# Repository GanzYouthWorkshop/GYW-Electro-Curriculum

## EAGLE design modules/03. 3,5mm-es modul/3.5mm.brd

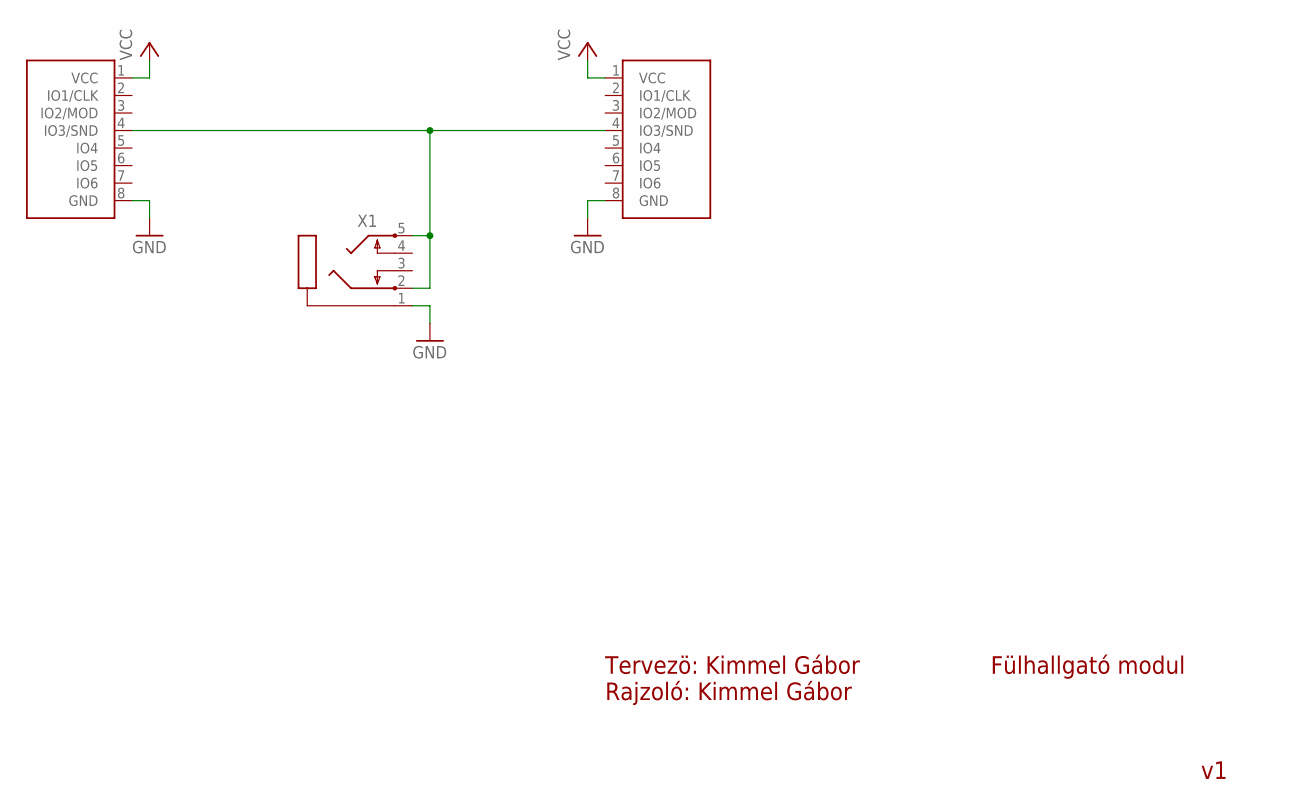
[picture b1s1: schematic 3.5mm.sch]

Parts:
U$1: GANZ-CONNECTOR; FE08W
U$2: GANZ-CONNECTOR-OUT; MA08-1W
X1: PG203J

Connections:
GND: U$1.8 (GND), U$2.8 (GND), X1.1
unnamed: U$1.4 (IO3/SND), U$2.4 (IO3/SND), X1.2, X1.5
VCC: U$1.1 (VCC), U$2.1 (VCC)

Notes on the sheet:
Fülhallgató modul
Tervezö: Kimmel Gábor Rajzoló: Kimmel Gábor

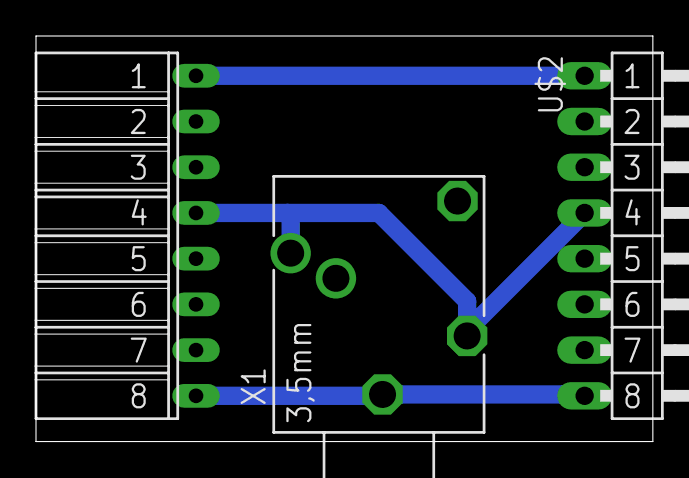
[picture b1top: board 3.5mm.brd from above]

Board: 2 copper layers, 34.3 x 22.5 mm, 3 parts (0 on the bottom side), 3 nets.

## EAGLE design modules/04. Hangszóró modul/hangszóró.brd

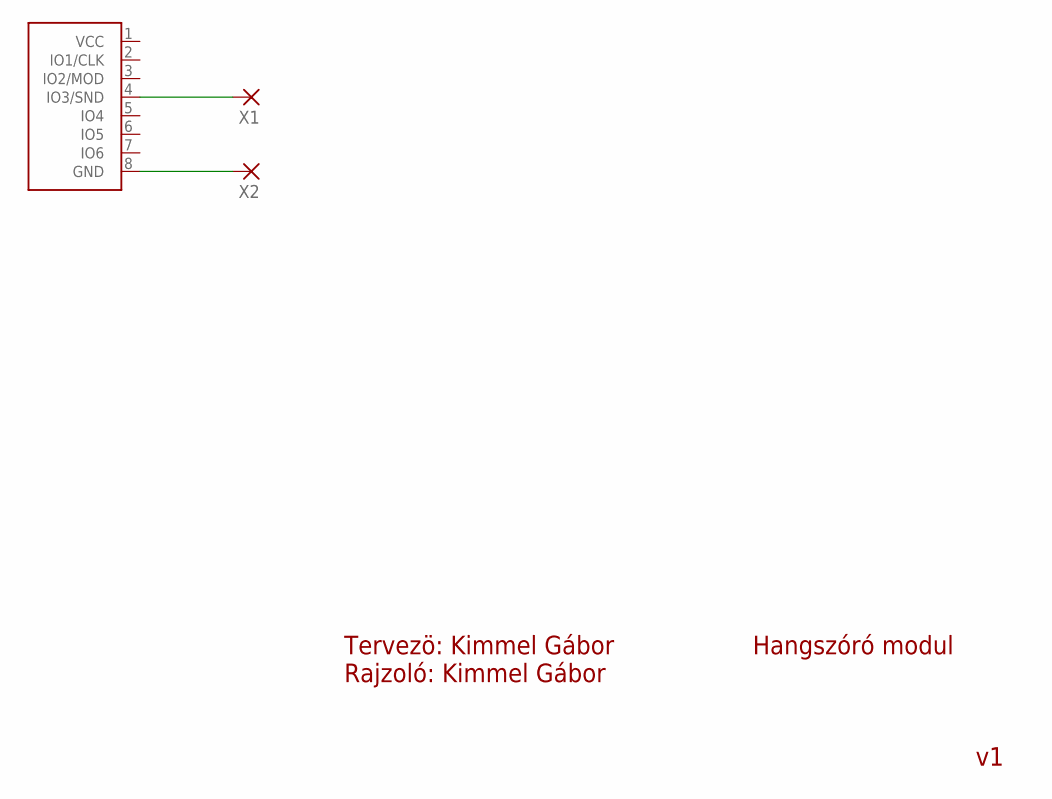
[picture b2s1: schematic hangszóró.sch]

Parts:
U$1: GANZ-CONNECTOR; FE08W
X1, X2: 2,15/1,0

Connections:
unnamed: U$1.4 (IO3/SND), X1.1
unnamed: U$1.8 (GND), X2.1

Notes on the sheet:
Hangszóró modul
Tervezö: Kimmel Gábor Rajzoló: Kimmel Gábor

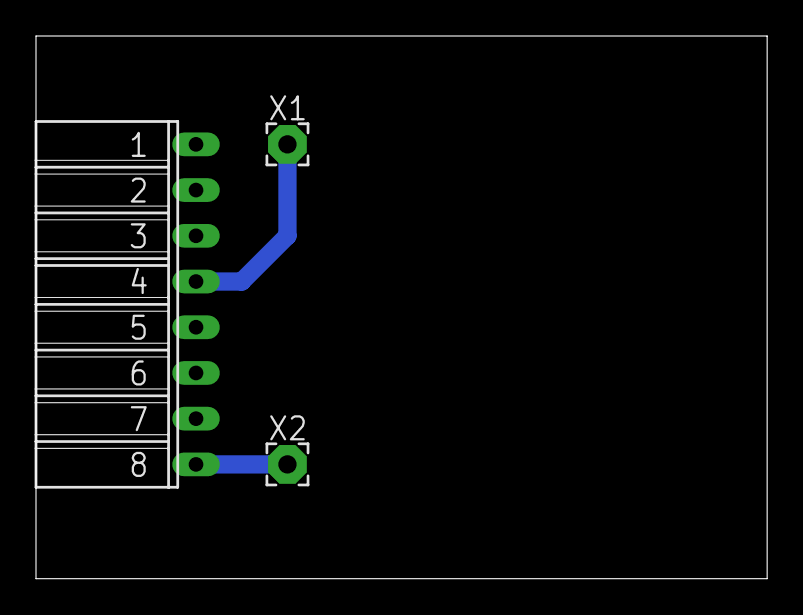
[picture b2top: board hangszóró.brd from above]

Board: 2 copper layers, 40.6 x 30.1 mm, 3 parts (0 on the bottom side), 2 nets.

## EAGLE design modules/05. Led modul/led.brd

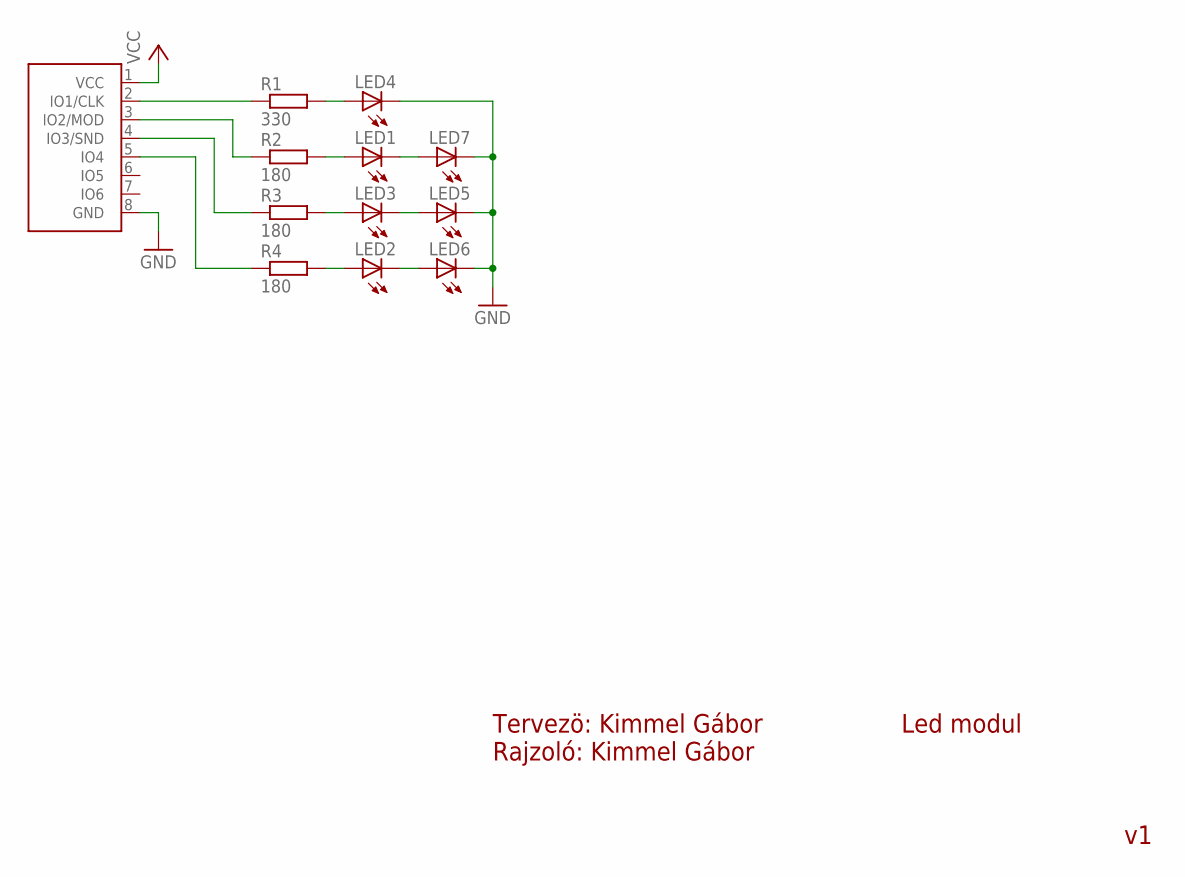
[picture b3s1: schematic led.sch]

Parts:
LED1, LED2, LED3, LED4, LED5, LED6, LED7: LED5MM
R1: 330; 0207/10
R2, R3, R4: 180; 0207/10
U$1: GANZ-CONNECTOR; FE08W

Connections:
GND: LED4.K (C), LED5.K (C), LED6.K (C), LED7.K (C), U$1.8 (GND)
unnamed: R1.1, U$1.2 (IO1/CLK)
unnamed: LED4.A, R1.2
unnamed: LED1.A, R2.2
unnamed: LED3.A, R3.2
unnamed: LED2.A, R4.2
unnamed: LED2.K (C), LED6.A
unnamed: LED3.K (C), LED5.A
unnamed: LED1.K (C), LED7.A
unnamed: R2.1, U$1.3 (IO2/MOD)
unnamed: R3.1, U$1.4 (IO3/SND)
unnamed: R4.1, U$1.5 (IO4)
VCC: U$1.1 (VCC)

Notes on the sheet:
Led modul
Tervezö: Kimmel Gábor Rajzoló: Kimmel Gábor

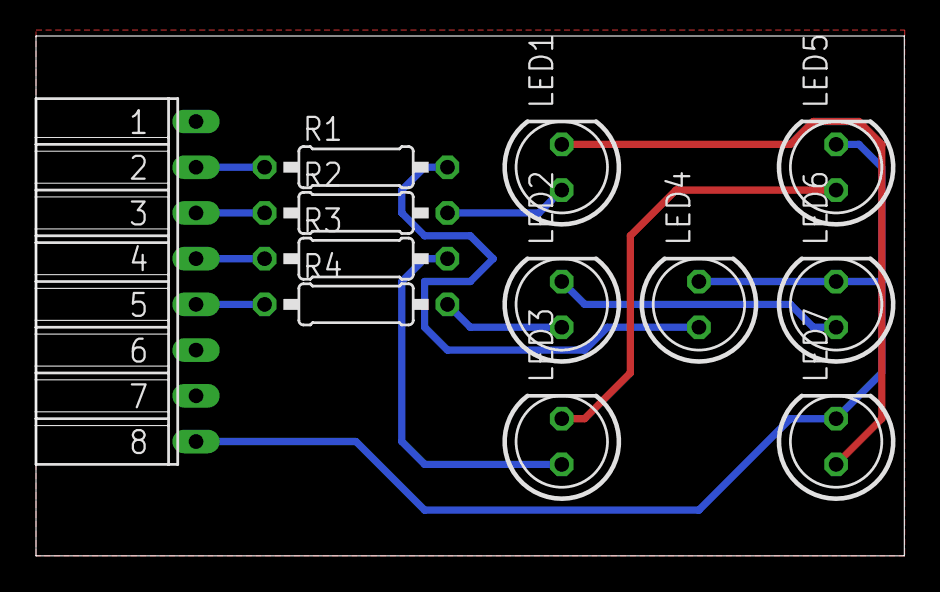
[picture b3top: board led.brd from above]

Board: 2 copper layers, 48.2 x 28.9 mm, 12 parts (0 on the bottom side), 12 nets.

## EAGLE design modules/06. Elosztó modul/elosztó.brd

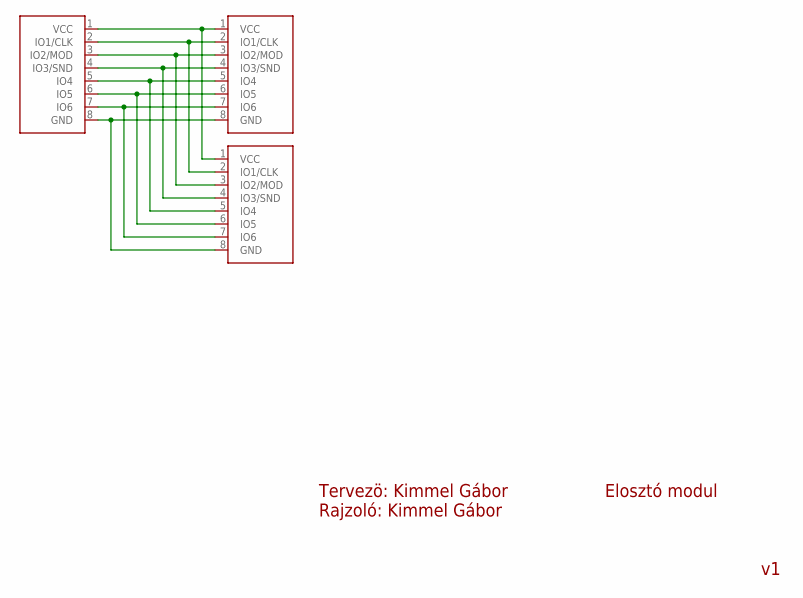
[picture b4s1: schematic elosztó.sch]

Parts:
U$1: GANZ-CONNECTOR; FE08W
U$2, U$3: GANZ-CONNECTOR-OUT; MA08-1W

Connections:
unnamed: U$1.1 (VCC), U$2.1 (VCC), U$3.1 (VCC)
unnamed: U$1.2 (IO1/CLK), U$2.2 (IO1/CLK), U$3.2 (IO1/CLK)
unnamed: U$1.3 (IO2/MOD), U$2.3 (IO2/MOD), U$3.3 (IO2/MOD)
unnamed: U$1.4 (IO3/SND), U$2.4 (IO3/SND), U$3.4 (IO3/SND)
unnamed: U$1.5 (IO4), U$2.5 (IO4), U$3.5 (IO4)
unnamed: U$1.6 (IO5), U$2.6 (IO5), U$3.6 (IO5)
unnamed: U$1.7 (IO6), U$2.7 (IO6), U$3.7 (IO6)
unnamed: U$1.8 (GND), U$2.8 (GND), U$3.8 (GND)

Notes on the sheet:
Elosztó modul
Tervezö: Kimmel Gábor Rajzoló: Kimmel Gábor

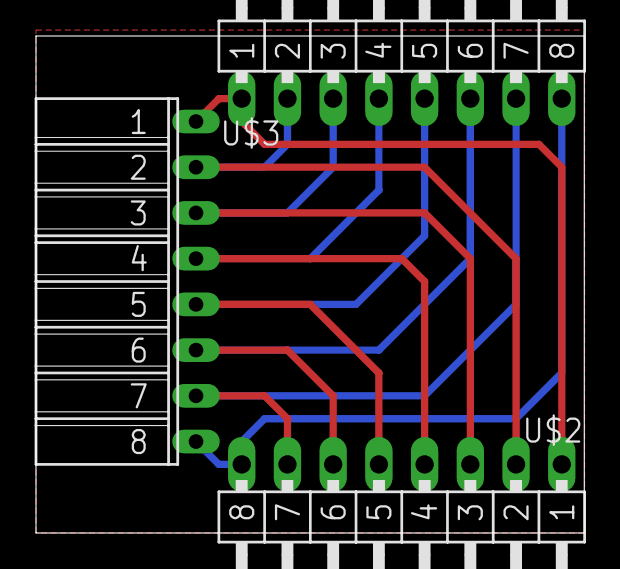
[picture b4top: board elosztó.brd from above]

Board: 2 copper layers, 30.5 x 27.6 mm, 3 parts (0 on the bottom side), 8 nets.

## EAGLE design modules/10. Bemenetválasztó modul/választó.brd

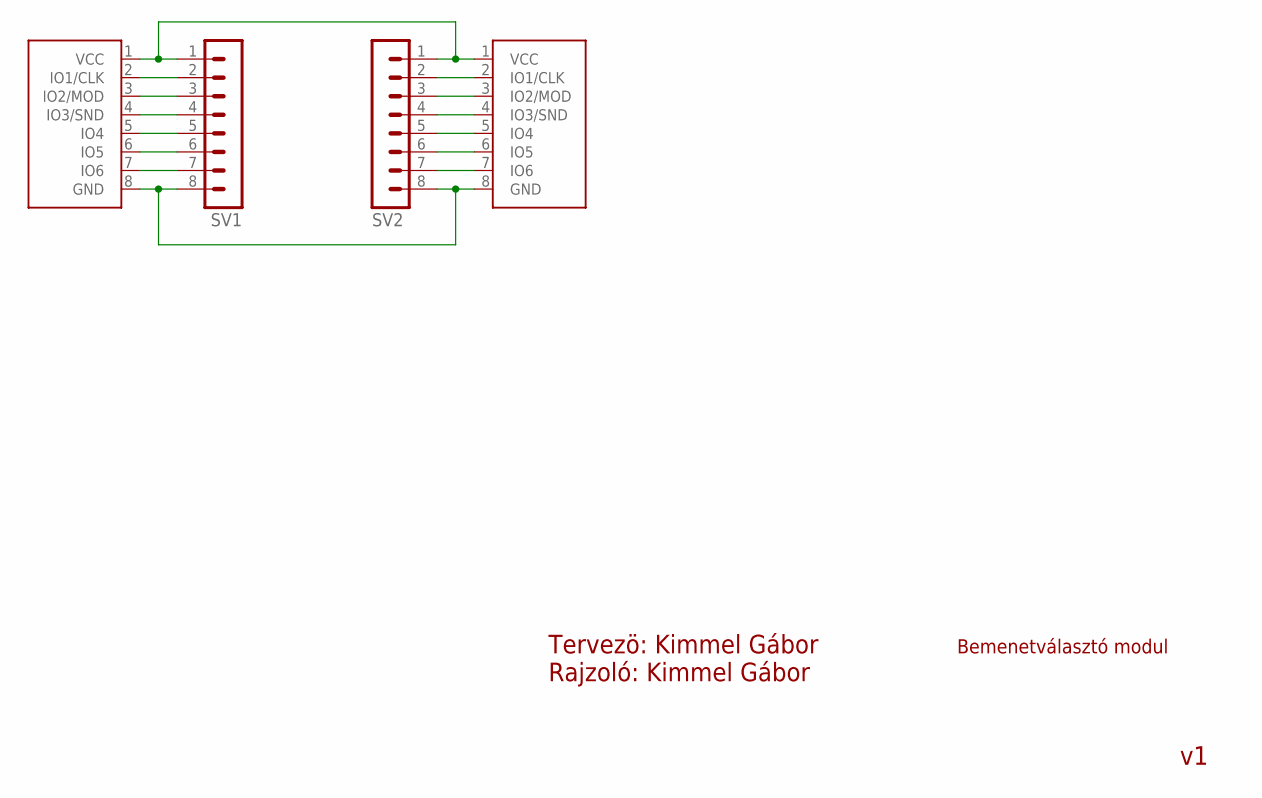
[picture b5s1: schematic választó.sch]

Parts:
SV1, SV2: MA08-1
U$1: GANZ-CONNECTOR; FE08W
U$2: GANZ-CONNECTOR-OUT; MA08-1W

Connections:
unnamed: SV1.1, SV2.1, U$1.1 (VCC), U$2.1 (VCC)
unnamed: SV1.2, U$1.2 (IO1/CLK)
unnamed: SV1.3, U$1.3 (IO2/MOD)
unnamed: SV1.4, U$1.4 (IO3/SND)
unnamed: SV1.5, U$1.5 (IO4)
unnamed: SV1.6, U$1.6 (IO5)
unnamed: SV1.7, U$1.7 (IO6)
unnamed: SV1.8, SV2.8, U$1.8 (GND), U$2.8 (GND)
unnamed: SV2.2, U$2.2 (IO1/CLK)
unnamed: SV2.3, U$2.3 (IO2/MOD)
unnamed: SV2.4, U$2.4 (IO3/SND)
unnamed: SV2.5, U$2.5 (IO4)
unnamed: SV2.6, U$2.6 (IO5)
unnamed: SV2.7, U$2.7 (IO6)

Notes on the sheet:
Bemenetválasztó modul
Tervezö: Kimmel Gábor Rajzoló: Kimmel Gábor

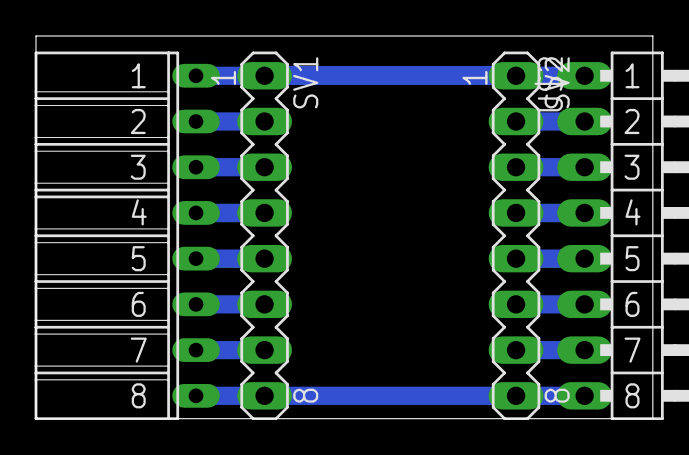
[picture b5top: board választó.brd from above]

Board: 2 copper layers, 34.3 x 21.3 mm, 4 parts (0 on the bottom side), 14 nets.

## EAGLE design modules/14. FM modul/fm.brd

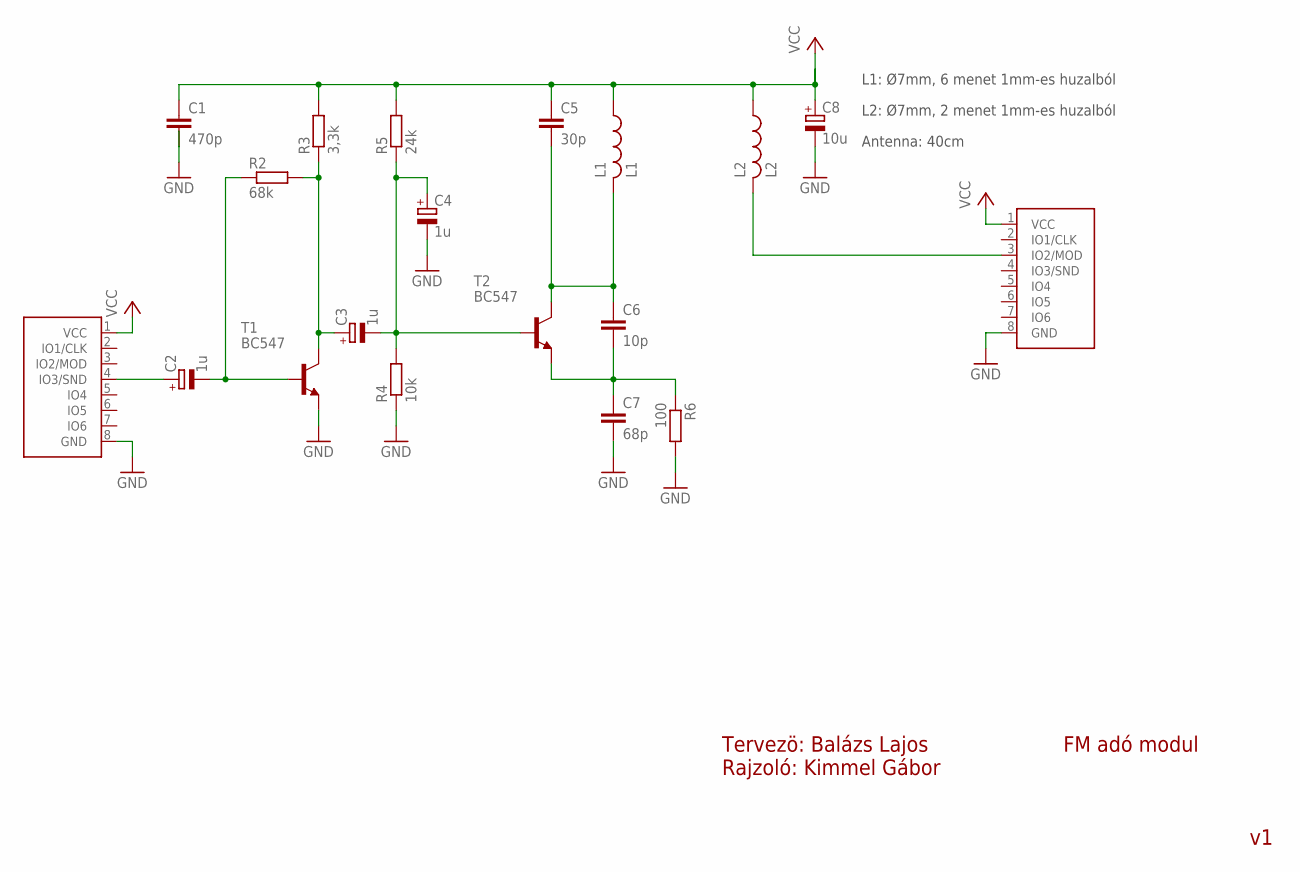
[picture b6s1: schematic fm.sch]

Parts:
C1: 470p; C075-032X103
C2, C3, C4: 1u; E2,5-7
C5: 30p; C075-032X103
C6: 10p; C075-032X103
C7: 68p; C075-032X103
C8: 10u; E2,5-7
L1: L1; 0207/7
L2: L2; 0207/7
R2: 68k; 0309/12
R3: 3,3k; 0309/12
R4: 10k; 0309/12
R5: 24k; 0309/12
R6: 100; 0309/12
T1, T2: BC547; TO92-CBE
U$1: GANZ-CONNECTOR; FE08W
U$2: GANZ-CONNECTOR-OUT; MA08-1W

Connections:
GND: C1.2, C4.-, C7.2, C8.-, R4.1, R6.2, T1.E, U$1.8 (GND), U$2.8 (GND)
unnamed: C2.+, U$1.4 (IO3/SND)
unnamed: C2.-, R2.1, T1.B
unnamed: C3.+, R2.2, R3.1, T1.C
unnamed: C3.-, C4.+, R4.2, R5.1, T2.B
unnamed: C6.2, C7.1, R6.1, T2.E
unnamed: C5.2, C6.1, L1.2, T2.C
unnamed: L2.2, U$2.3 (IO2/MOD)
VCC: C1.1, C5.1, C8.+, L1.1, L2.1, R3.2, R5.2, U$1.1 (VCC), U$2.1 (VCC)

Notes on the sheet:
L1: Ø7mm, 6 menet 1mm-es huzalból
L2: Ø7mm, 2 menet 1mm-es huzalból
Antenna: 40cm
FM adó modul
Tervezö: Balázs Lajos Rajzoló: Kimmel Gábor

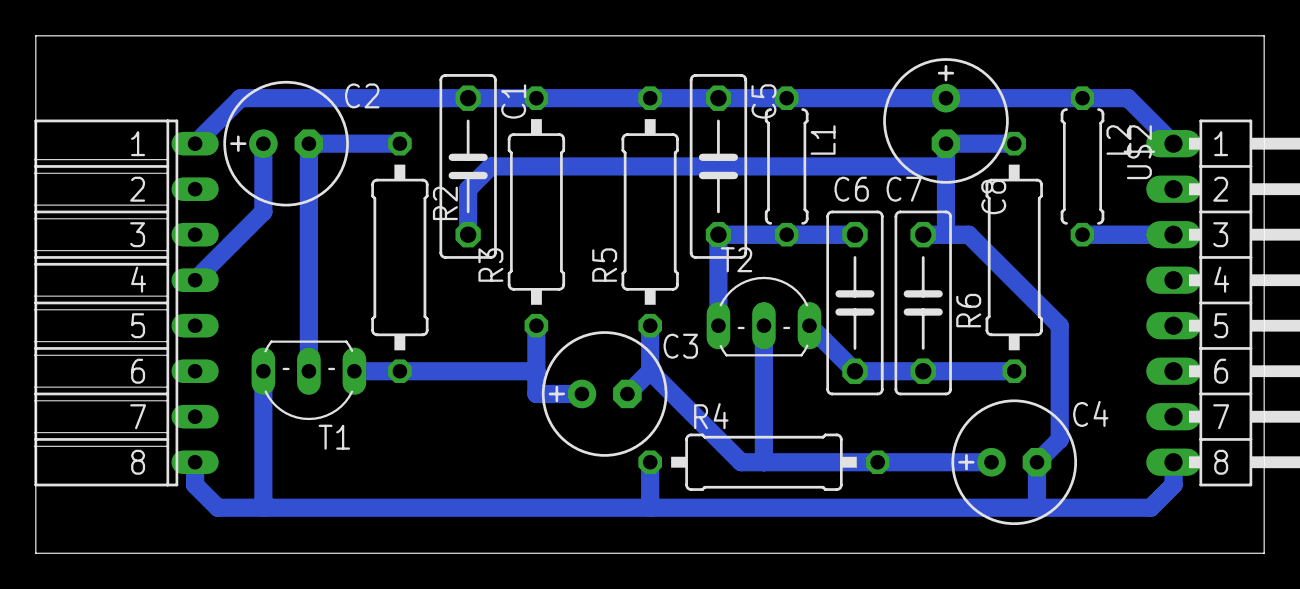
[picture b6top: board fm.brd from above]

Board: 2 copper layers, 68.6 x 28.9 mm, 19 parts (0 on the bottom side), 9 nets.

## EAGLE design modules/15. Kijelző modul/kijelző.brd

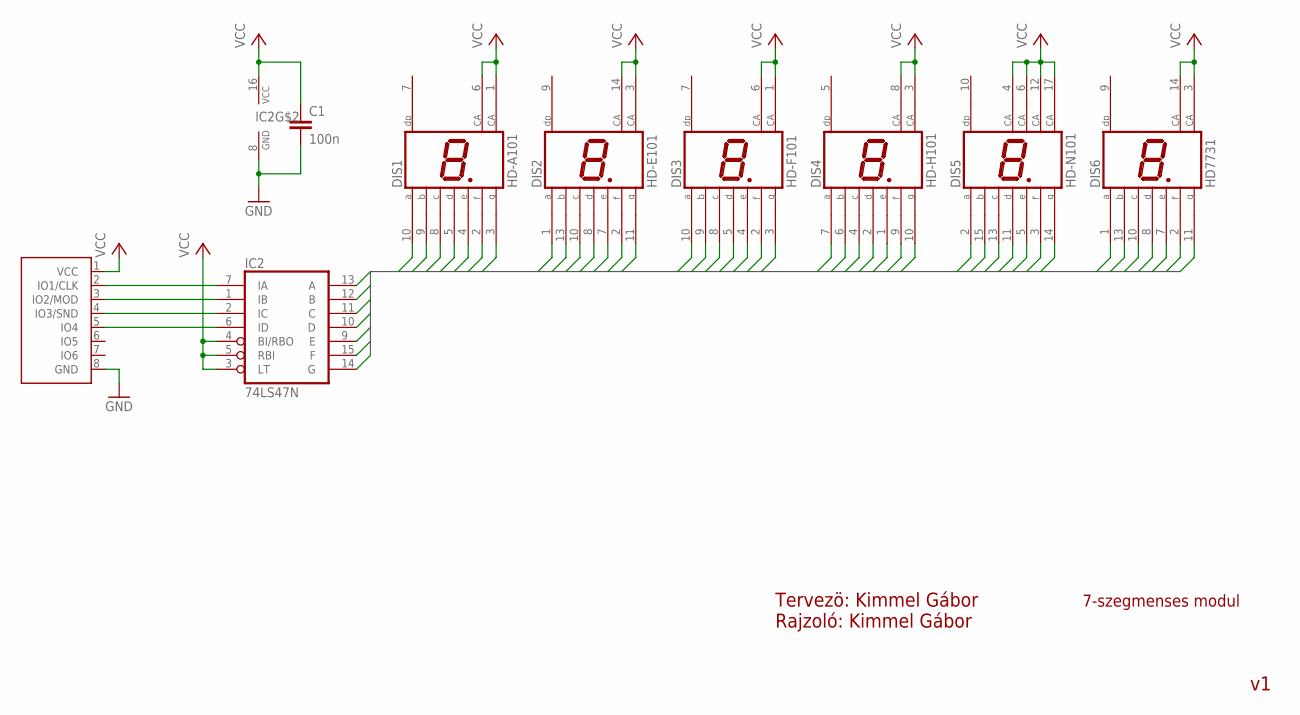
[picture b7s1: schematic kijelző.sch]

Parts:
C1: 100n; C075-032X103
DIS1: HD-A101; HDSP-A
DIS2: HD-E101; HDSP-I
DIS3: HD-F101; HDSP-E
DIS4: HD-H101; HDSP-M
DIS5: HD-N101; HDSP-Q
DIS6: HD7731; HD7730
IC2: 74LS47N; DIL16
U$1: GANZ-CONNECTOR; FE08W

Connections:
A: DIS1.10 (A), DIS2.1 (A), DIS3.10 (A), DIS4.7 (A), DIS5.2 (A), DIS6.1 (A), IC2.13 (A)
B: DIS1.9 (B), DIS2.13 (B), DIS3.9 (B), DIS4.6 (B), DIS5.15 (B), DIS6.13 (B), IC2.12 (B)
C: DIS1.8 (C), DIS2.10 (C), DIS3.8 (C), DIS4.4 (C), DIS5.13 (C), DIS6.10 (C), IC2.11 (C)
D: DIS1.5 (D), DIS2.8 (D), DIS3.5 (D), DIS4.2 (D), DIS5.11 (D), DIS6.8 (D), IC2.10 (D)
E: DIS1.4 (E), DIS2.7 (E), DIS3.4 (E), DIS4.1 (E), DIS5.5 (E), DIS6.7 (E), IC2.9 (E)
F: DIS1.2 (F), DIS2.2 (F), DIS3.2 (F), DIS4.9 (F), DIS5.3 (F), DIS6.2 (F), IC2.15 (F)
G: DIS1.3 (G), DIS2.11 (G), DIS3.3 (G), DIS4.10 (G), DIS5.14 (G), DIS6.11 (G), IC2.14 (G)
GND: C1.2, IC2.8 (GND), U$1.8 (GND)
unnamed: IC2.7 (IA), U$1.2 (IO1/CLK)
unnamed: IC2.1 (IB), U$1.3 (IO2/MOD)
unnamed: IC2.2 (IC), U$1.4 (IO3/SND)
unnamed: IC2.6 (ID), U$1.5 (IO4)
VCC: C1.1, DIS1.1 (CA), DIS1.6 (CA), DIS2.3 (CA), DIS2.14 (CA), DIS3.1 (CA), DIS3.6 (CA), DIS4.3 (CA), DIS4.8 (CA), DIS5.4 (CA), DIS5.6 (CA), DIS5.12 (CA), DIS5.17 (CA), DIS6.3 (CA), DIS6.14 (CA), IC2.3 (LT), IC2.4 (BI/RBO), IC2.5 (RBI), IC2.16 (VCC), U$1.1 (VCC)

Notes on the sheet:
7-szegmenses modul
Tervezö: Kimmel Gábor Rajzoló: Kimmel Gábor

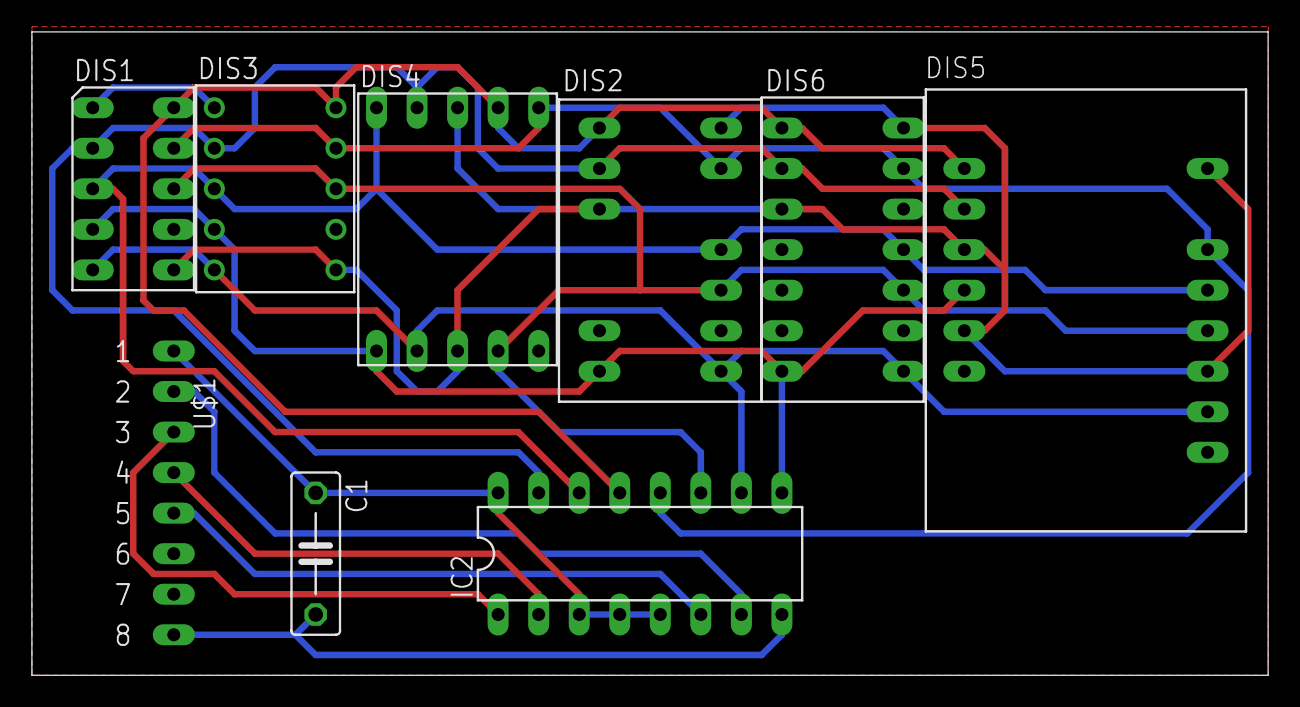
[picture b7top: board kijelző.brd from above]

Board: 2 copper layers, 77.5 x 40.3 mm, 9 parts (0 on the bottom side), 13 nets.
